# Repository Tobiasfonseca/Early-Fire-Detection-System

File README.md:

# Early-Fire-Detection-System
Sistema para detección temprana de incendios.

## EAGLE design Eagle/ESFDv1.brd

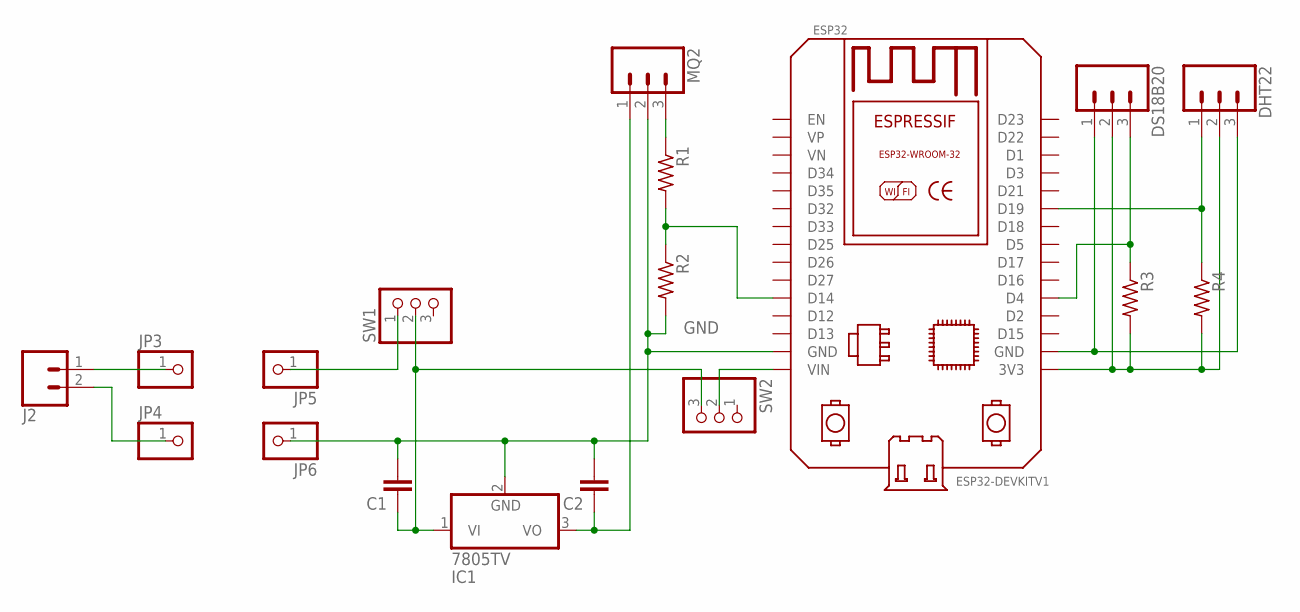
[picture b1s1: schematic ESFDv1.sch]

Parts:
C1, C2: C5/2.5; C5B2.5
DHT22: CONN_03-SCREW-5MM; SCREWTERMINAL-5MM-3
DS18B20: CONN_03-SCREW-5MM; SCREWTERMINAL-5MM-3
ESP32: ESP32DEVKITV1; ESP32-DEVKITV1
IC1: 7805TV; TO220V
J2: CONN_025MM; SCREWTERMINAL-5MM-2
JP3, JP4, JP5, JP6: PINHD-1X1; 1X01
MQ2: CONN_03-SCREW-5MM; SCREWTERMINAL-5MM-3
R1, R2: R-US_0309/12; 0309/12
R3, R4: R-US_0414/15; 0414/15
SW1, SW2: PINHD-1X3; 1X03

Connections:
3.3V: DHT22.2, DS18B20.2, ESP32.3V3, R3.2, R4.2
D_DHT22: DHT22.1, ESP32.D19, R4.1
D_DS18B20: DS18B20.3, ESP32.D4, R3.1
GND: C1.2, C2.2, DHT22.3, DS18B20.1, ESP32.GND, ESP32.GND@1 (GND), IC1.2 (GND), JP6.1, MQ2.2, R2.2
unnamed: J2.1, JP3.1
unnamed: J2.2, JP4.1
unnamed: JP5.1, SW1.1
unnamed: MQ2.3, R1.1
unnamed: ESP32.D14, R1.2, R2.1
unnamed: C1.1, IC1.1 (VI), SW1.2, SW2.3
unnamed: ESP32.VIN, SW2.2
unnamed: C2.1, IC1.3 (VO), MQ2.1

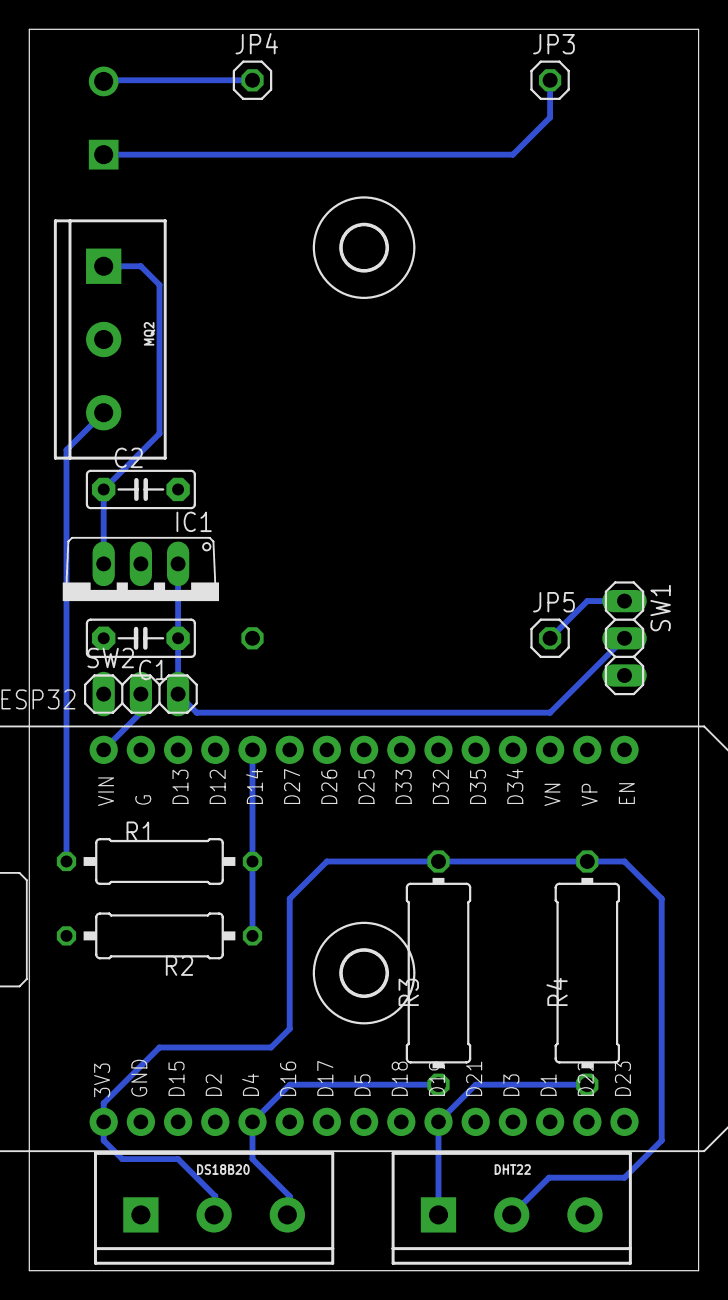
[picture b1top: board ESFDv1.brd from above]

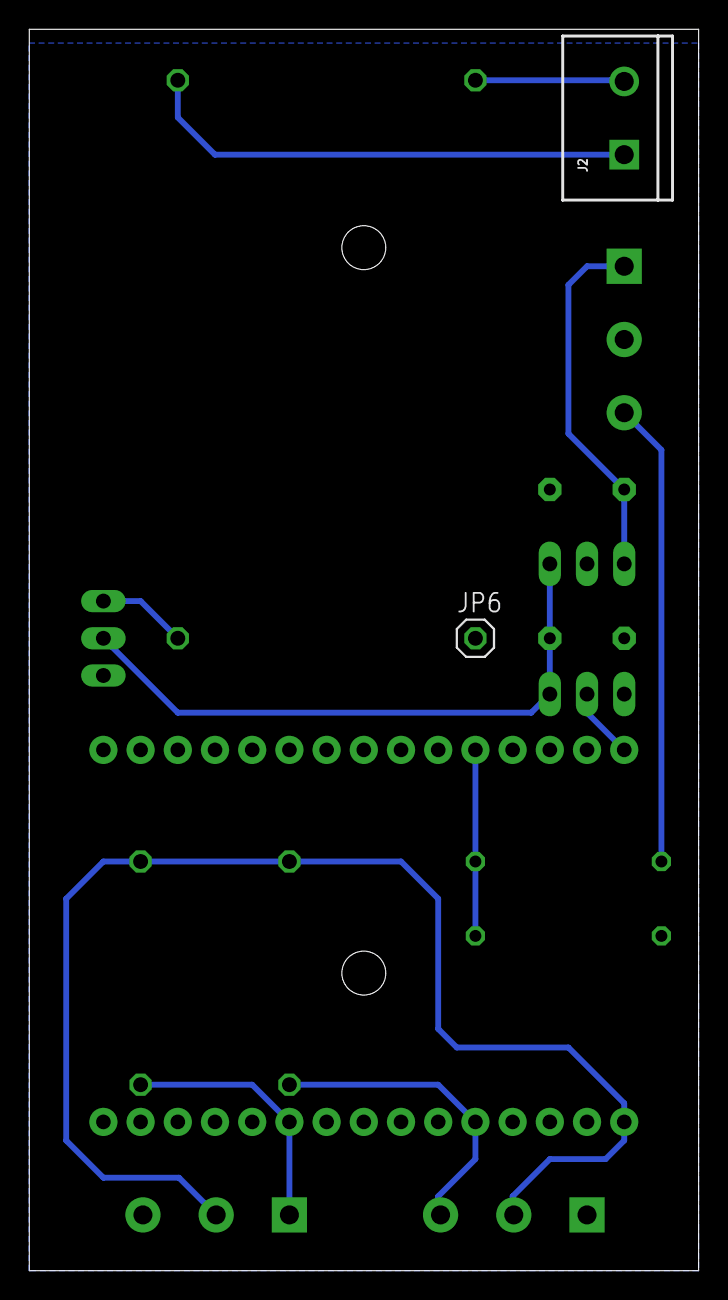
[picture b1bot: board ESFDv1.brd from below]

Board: 2 copper layers, 45.7 x 84.8 mm, 20 parts (2 on the bottom side), 12 nets.

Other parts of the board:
U$1, U$2: 3,0

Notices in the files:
parts and their libraries:
SparkFun-Connectors: Licensing: Creative Commons ShareAlike 4.0 International - https://creativecommons.org/licenses/by-sa/4.0
